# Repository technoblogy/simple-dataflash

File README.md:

# Simple DataFlash
A simple DataFlash library for sequential reading and writing. For more information, and the circuit for a simple DataFlash board, see: <http://www.technoblogy.com/show?2JMU>.

The DataFlash library consists of the following seven routines:

#### DataFlash.Setup()

Must be called once to set up the I/O lines to interface with the DataFlash chip. It returns true if the flash chip was found successfully.

#### DataFlash.BeginWrite()

Call this once before writing to the DataFlash. It erases the entire DataFlash chip and sets the address pointer to the start of the chip.

#### DataFlash.WriteByte(uint8_t byte)

Writes a byte of data to the next DataFlash memory location.

#### DataFlash.EndWrite()

Call this once after writing to the DataFlash.

#### DataFlash.BeginRead(unsigned long addr)

Call this once before reading from the DataFlash with the start address for reading.

#### DataFlash.ReadByte()

Reads and returns a byte of data from the next DataFlash memory location.

#### DataFlash.EndRead()

Call this once after reading from the DataFlash.

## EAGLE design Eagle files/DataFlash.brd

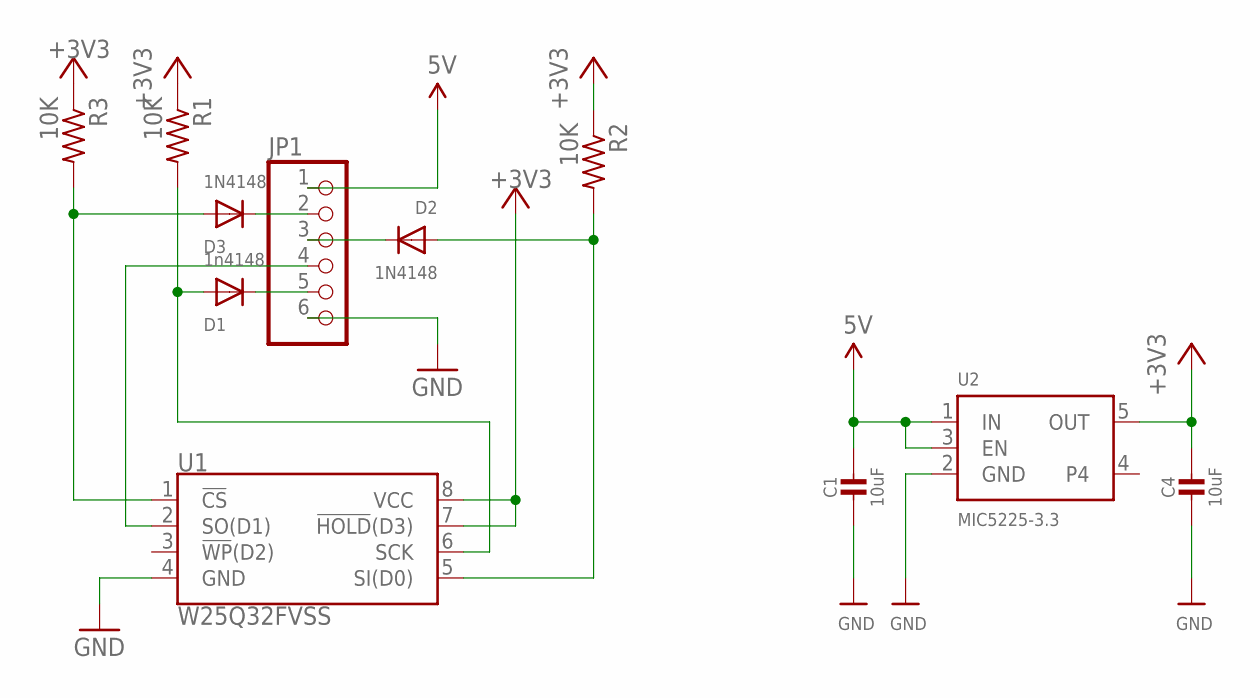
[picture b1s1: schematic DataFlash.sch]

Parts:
C1, C4: 10uF; 0805-NO
D1: 1n4148; SOD-323F
D2, D3: 1N4148; SOD-323F
JP1: HEADER-1X6ROUND; 1X06_ROUND
R1, R2, R3: 10K; R0805
U1: W25Q32FVSS; SOIC-8
U2: MIC5225-3.3; SOT23-5

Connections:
5V: C1.1, JP1.1, U2.1 (IN), U2.3 (EN)
+3V3: C4.1, R1.1, R2.1, R3.1, U1.7 (!HOLD!(D3)), U1.8 (VCC), U2.5 (OUT)
GND: C1.2, C4.2, JP1.6, U1.4 (GND), U2.2 (GND)
unnamed: D2.C, JP1.3
unnamed: D1.C, JP1.5
unnamed: D2.A, R2.2, U1.5 (SI(D0))
unnamed: D3.C, JP1.2
unnamed: D3.A, R3.2, U1.1 (!CS!)
PB11_S4_SPI_SCK: D1.A, R1.2, U1.6 (SCK)
PB12_S4_SPI_MISO: JP1.4, U1.2 (SO(D1))

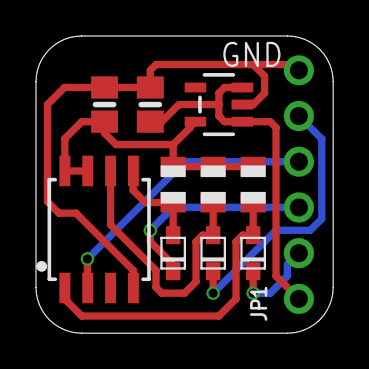
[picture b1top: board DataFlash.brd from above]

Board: 2 copper layers, 16.5 x 16.5 mm, 11 parts (0 on the bottom side), 10 nets.

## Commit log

2019-07-17 Version 1 - 17th July 2019

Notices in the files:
parts and their libraries:
SparkFun-DigitalIC: Licensing: Creative Commons ShareAlike 4.0 International - https://creativecommons.org/licenses/by-sa/4.0
microbuilder: This work is placed in the public domain, and may be freely used for commercial and non-commercial work with the following conditions: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
